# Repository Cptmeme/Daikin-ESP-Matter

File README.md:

# ESP-Matter-Daikin-S21

ESP32 project to get matter to work with my Daikin A/C with a S21 port.

## Firmware

- Heating/cooling supported.
- Still some bugs to iron out but basic functionality now works!

### TODO
- Has been tested to work with the custom PCB provided in this repo connected to a Daikin FTXM25R5V1B

### Sources

Code copied or inspiration taken from:

- https://github.com/espressif/esp-matter (copied example code for A/C)
- https://github.com/revk/ESP32-Faikin (taken s21 protocol files)
- https://github.com/asund/esphome-daikin-s21 (inspiration)

## Custom PCB
Based on an esp32c6-mini-1 to allow for thread support, has been verified to work in esphome using asund's esphome-daikin-s21 code.

### WARNING!
Do not connect the pcb to the A/C and a PC over the usb-c port at the same time as this will short out your usb port!

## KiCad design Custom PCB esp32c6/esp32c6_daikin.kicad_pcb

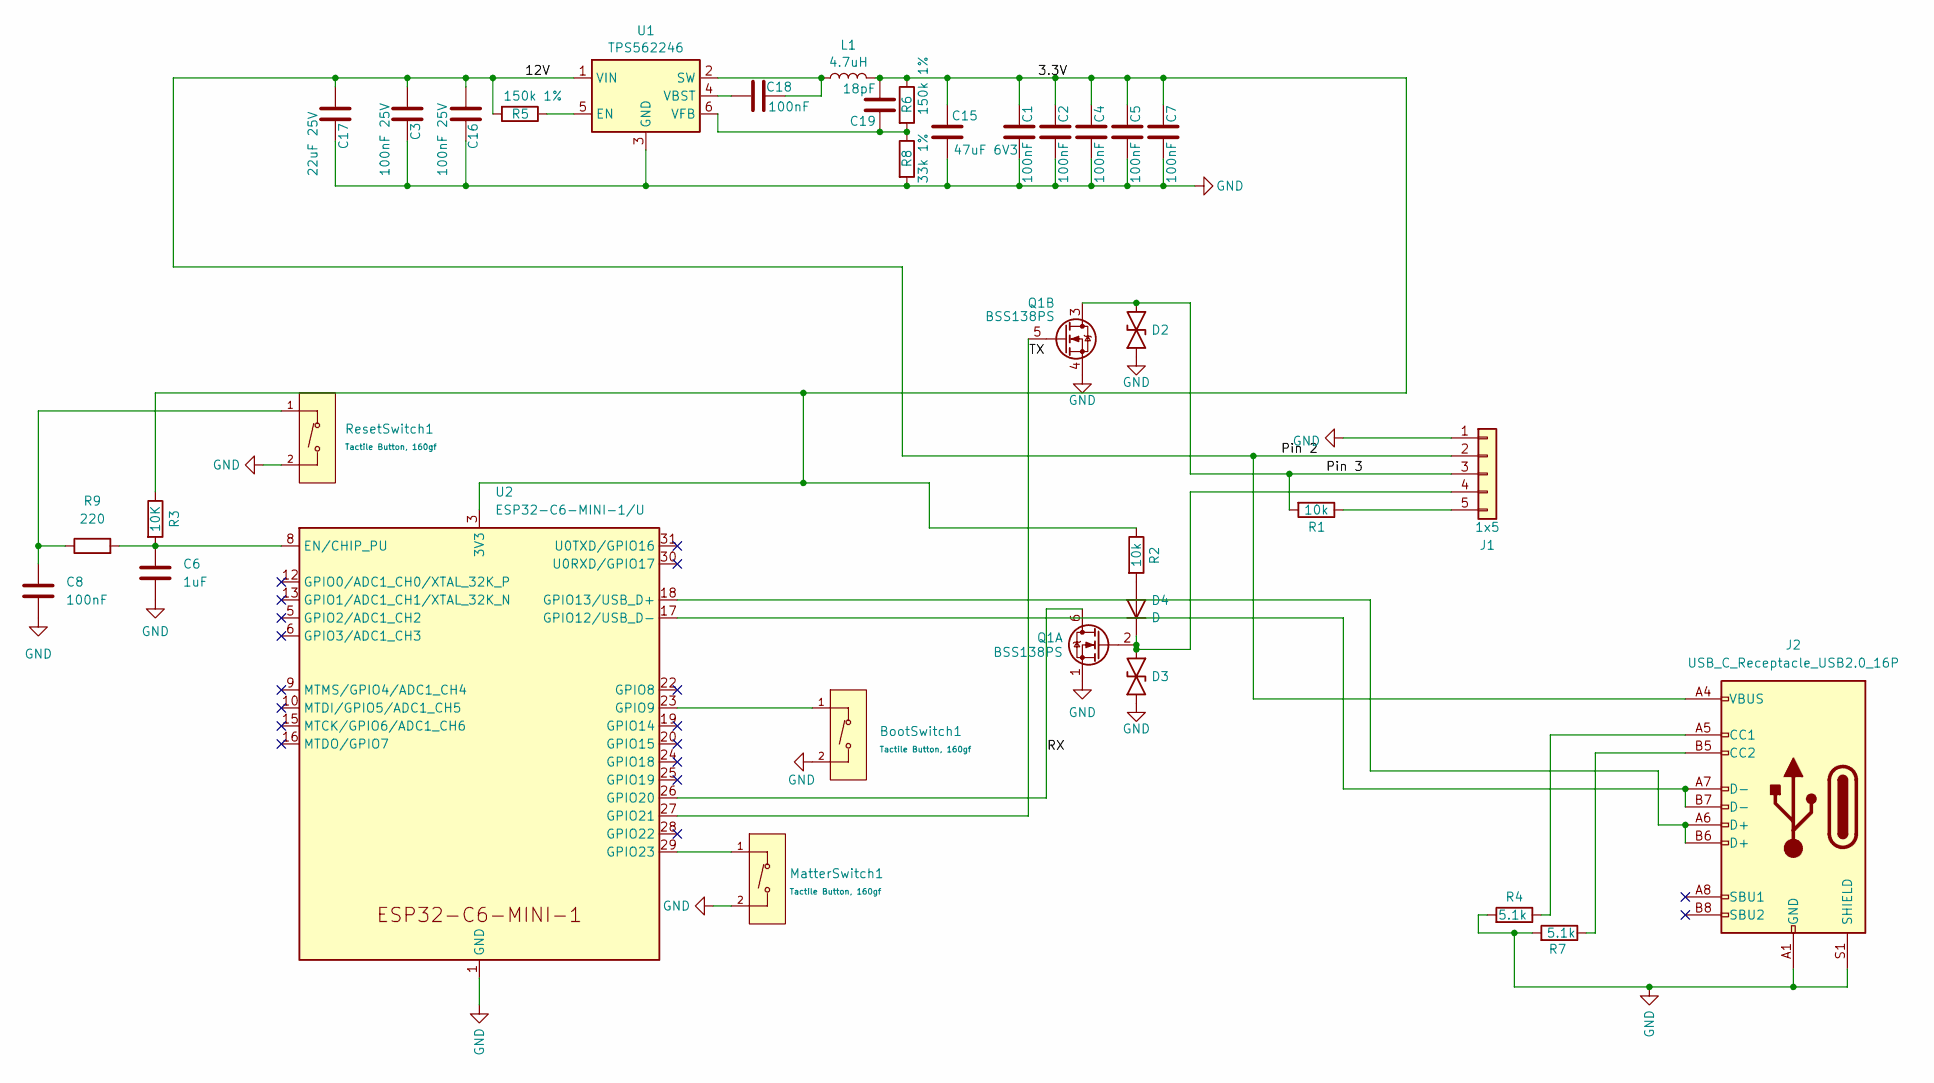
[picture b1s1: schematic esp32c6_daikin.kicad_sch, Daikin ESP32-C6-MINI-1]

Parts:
BootSwitch1: Tactile Button, 160gf; SW_TS-1088-AR02016; Voltage Rating (Dc) 12V; Part TS-1088-AR02016; LCSC C720477
C1, C2, C4, C5, C7, C8, C18: 100nF; C0402; LCSC C1525
C3, C16: 100nF 25V; C0402; LCSC C307331
C6: 1uF; C0603; LCSC C15849
C15: 47uF 6V3; C0805; LCSC C16780
C17: 22uF 25V; C0805; LCSC C45783
C19: 18pF; C0402; LCSC C1549
D2, D3: DFN1006-2L_L1.0-W0.6-P0.65-BI; MPN C5137770
D4: D; D0402; MPN C28642302
J1: 1x5; CONN-TH_S5B-EH-LF-SN; MPN C265103
J2: USB_C_Receptacle_USB2.0_16P; USB_C_Receptacle_GCT_USB4105-xx-A_16P_TopMnt_Horizontal
L1: 4.7uH; IND-SMD_L4.9-W4.9_NRS50XX; LCSC C307876
MatterSwitch1: Tactile Button, 160gf; SW_TS-1088-AR02016; Voltage Rating (Dc) 12V; Part TS-1088-AR02016; LCSC C720477
Q1: BSS138PS; SOT-363_L2.0-W1.3-P0.65-LS2.1-BR; MPN C193381
R1, R2: 10k; R0402; MPN C25744
R3: 10K; R0402; LCSC C25744
R4, R7: 5.1k; R0402; LCSC C25905
R5, R6: 150k 1%; R0603; LCSC C22807
R8: 33k 1%; R0402; LCSC C25779
R9: 220; R0402; LCSC C25091
ResetSwitch1: Tactile Button, 160gf; SW_TS-1088-AR02016; Voltage Rating (Dc) 12V; Part TS-1088-AR02016; LCSC C720477
U1: TPS562246; SOT-5X3-6_L1.6-W1.2-P0.50-LS1.6-BR; LCSC C41833479
U2: ESP32-C6-MINI-1/U; ESP32-C6-MINI-1; LCSC C5736265

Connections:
/3.3V: C1.2, C2.2, C4.2, C5.2, C7.2, C15.1, C19.2, L1.2, R2.1, R3.1, R6.1, U2.3 (3V3)
/12V: C3.1, C16.1, C17.1, J1.2, J2.A4 (VBUS), J2.A9 (VBUS), J2.B4 (VBUS), J2.B9 (VBUS), R5.2, U1.1 (VIN)
/Pin 3: D2.2, J1.3, Q1.3 (SP), R1.2
/RX: Q1.6 (DN), U2.26 (GPIO20)
/TX: Q1.5 (GP), U2.27 (GPIO21)
GND: BootSwitch1.2 (B), C1.1, C2.1, C3.2, C4.1, C5.1, C6.2, C7.1, C8.2, C15.2, C16.2, C17.2, D2.1, D3.1, J1.1, J2.A1 (GND), J2.A12 (GND), J2.B1 (GND), J2.B12 (GND), J2.S1 (SHIELD), MatterSwitch1.2 (B), Q1.1 (SN), Q1.4 (DP), R4.2, R7.2, R8.2, ResetSwitch1.2 (B), U1.3 (GND), U2.1 (GND), U2.2 (GND), U2.11 (GND), U2.14 (GND), U2.36 (GND), U2.37 (GND), U2.38 (GND), U2.39 (GND), U2.40 (GND), U2.41 (GND), U2.42 (GND), U2.43 (GND), U2.44 (GND), U2.45 (GND), U2.46 (GND), U2.47 (GND), U2.48 (GND), U2.49 (GND), U2.50 (GND), U2.51 (GND), U2.52 (GND), U2.53 (GND)
unnamed: BootSwitch1.1 (A), U2.23 (GPIO9)
unnamed: D4.2 (A), R2.2
unnamed: D3.2, D4.1 (K), J1.4, Q1.2 (GN)
unnamed: J1.5, R1.1
unnamed: J2.A5 (CC1), R4.1
unnamed: J2.B5 (CC2), R7.1
unnamed: MatterSwitch1.1 (A), U2.29 (GPIO23)
unnamed: C8.1, R9.1, ResetSwitch1.1 (A)
unnamed: R5.1, U1.5 (EN)
unnamed: C18.2, L1.1, U1.2 (SW)
unnamed: C18.1, U1.4 (VBST)
unnamed: C19.1, R6.2, R8.1, U1.6 (VFB)
unnamed: C6.1, R3.2, R9.2, U2.8 (EN/CHIP_PU)
unnamed: J2.A7 (D-), J2.B7 (D-), U2.17 (GPIO12/USB_D-)
unnamed: J2.A6 (D+), J2.B6 (D+), U2.18 (GPIO13/USB_D+)

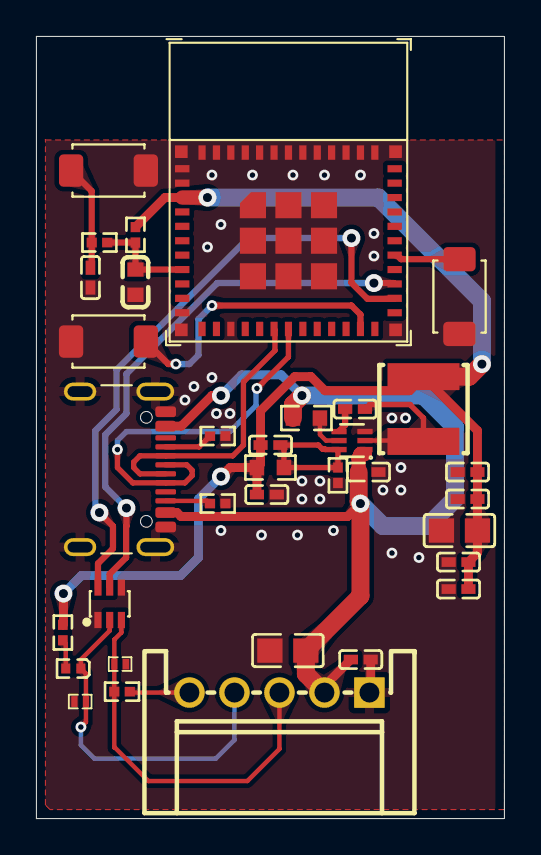
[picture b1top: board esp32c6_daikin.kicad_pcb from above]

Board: 2 copper layers, 26.0 x 43.5 mm, 34 parts (0 on the bottom side), 21 nets.

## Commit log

2025-04-24 Create test
2025-04-24 Rename CMakeLists.txt to main/CMakeLists.txt
2025-04-24 Rename Debug.h to main/Debug.h
2025-04-24 Rename IS21Protocol.h to main/IS21Protocol.h
2025-04-24 Rename IThermostatControl.h to main/IThermostatControl.h
2025-04-24 Rename S21Protocol.cpp to main/S21Protocol.cpp
2025-04-24 Rename S21Protocol.h to main/S21Protocol.h
2025-04-24 Rename S21Utils.h to main/S21Utils.h
2025-04-24 Rename ThermostatController.cpp to main/ThermostatController.cpp
2025-04-24 Rename ThermostatController.h to main/ThermostatController.h
2025-04-24 Rename ThermostatMode.h to main/ThermostatMode.h
2025-04-24 Rename app_driver_room_air_conditioner.cpp to main/app_driver_room_air_conditioner.cpp
2025-04-24 Rename app_driver_room_air_conditioner.h to main/app_driver_room_air_conditioner.h
2025-04-24 Rename app_main.cpp to main/app_main.cpp
2025-04-24 Rename app_priv.h to main/app_priv.h
2025-04-24 Rename idf_component.yml to main/idf_component.yml
2025-11-25 Custom PCB Design
    Does it look nice? - No,
    Is it well optimized? -Also no,
    Does it work? -Yes it does!
2025-11-25 basic thermostat example for matter
2025-11-25 Update README with custom PCB and main code information
    Added details about custom PCB and main code usage.
2025-11-25 Update project status to 'Work in progress'
2025-12-03 Working Daikin code!!!
    It finally works!!
2025-12-05 Refactor README.md for better organization
    Updated README.md to improve structure and clarity, added sections for firmware, TODO, sources, custom PCB, and warning.
